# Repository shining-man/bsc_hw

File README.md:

# Battery safety controller (BSC)
This is the PCB for the Battery safety controller.<br>
More information in the wiki and in the discussions of the bsc_fw project.<br>
[BSC Project](https://github.com/shining-man/bsc_fw)<br>
[Wiki (German)](https://github.com/shining-man/bsc_fw/wiki)<br>
[Discussions](https://github.com/shining-man/bsc_fw/discussions)<br>
<br>

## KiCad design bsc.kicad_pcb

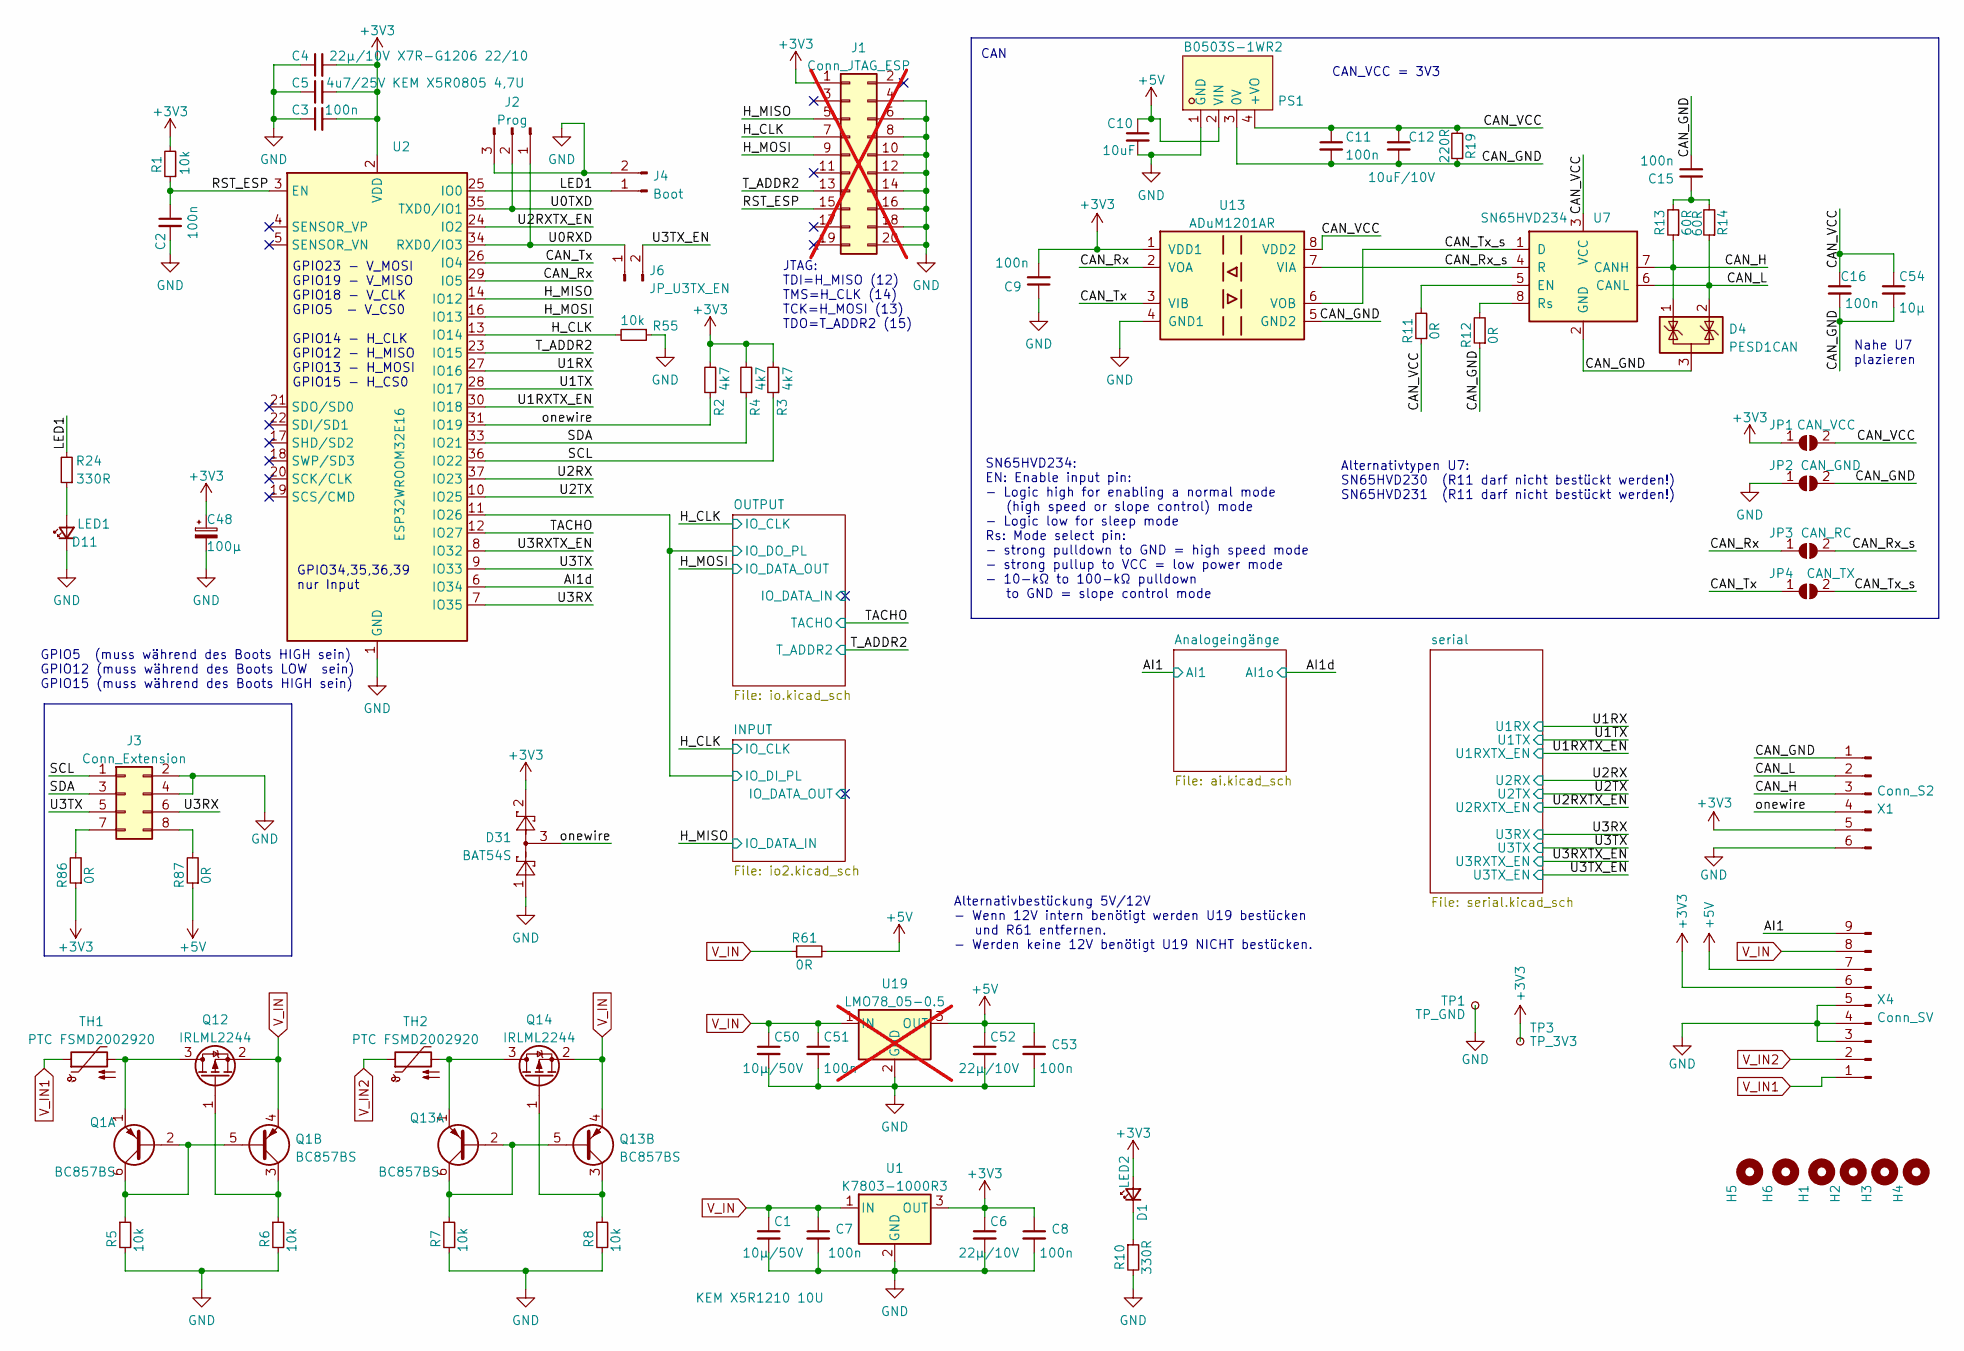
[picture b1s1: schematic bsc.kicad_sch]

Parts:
C1, C50: 10µ/50V; C_1206_3216Metric
C2, C3, C7, C8, C9, C11, C15, C16, C51, C53: 100n; C_0603_1608Metric
C4, C6, C52: 22µ/10V; C_1206_3216Metric
C5: 4u7/25V; C_0805_2012Metric
C10: 10uF; C_0603_1608Metric
C12: 10uF/10V; C_1206_3216Metric
C48: 100µ; CP_Elec_6.3x5.9
C54: 10µ; C_0805_2012Metric
D1: LED2; LED_0603_1608Metric
D4: PESD1CAN; SOT-23
D11: LED1; LED_0603_1608Metric
D31: BAT54S; SOT-23
H1, H2, H3, H4, H5, H6: MountingHole; MountingHole_3.2mm_M3
J1: Conn_JTAG_ESP; PinHeader_2x10_P1.27mm_Vertical_SMD; not fitted
J2: Prog; PinHeader_1x03_P2.54mm_Vertical_jlc
J3: Conn_Extension; PinHeader_2x04_P2.54mm_Vertical_jlc
J4: Boot; PinHeader_1x02_P2.54mm_Vertical_jlc
J6: JP_U3TX_EN; PinHeader_1x02_P2.54mm_Vertical_jlc
JP1: CAN_VCC; SolderJumper-2_P1.3mm_Open_RoundedPad1.0x1.5mm
JP2: CAN_GND; SolderJumper-2_P1.3mm_Open_RoundedPad1.0x1.5mm
JP3: CAN_RC; SolderJumper-2_P1.3mm_Open_RoundedPad1.0x1.5mm
JP4: CAN_TX; SolderJumper-2_P1.3mm_Open_RoundedPad1.0x1.5mm
PS1: B0503S-1WR2; PWRM-TH_DEXU_BXXXXS-1WR2; LCSC Part C5127059
Q1, Q13: BC857BS; SOT-363_SC-70-6
Q12, Q14: IRLML2244; SOT-23
R1, R5, R6, R7, R8, R55: 10k; R_0603_1608Metric
R2, R3, R4: 4k7; R_0603_1608Metric
R10, R24: 330R; R_0603_1608Metric
R11, R12, R61, R86, R87: 0R; R_0603_1608Metric
R13, R14: 60R; R_0603_1608Metric
R19: 220R; R_0805_2012Metric
TH1, TH2: PTC FSMD2002920; Fuse_2920_7451Metric
TP1: TP_GND; TestPoint_Pad_1.0x1.0mm
TP3: TP_3V3; TestPoint_Pad_1.0x1.0mm
U1: K7803-1000R3; Converter_DCDC_RECOM_R-78E-1.0; LCSC Part C111278
U2: ESP32WROOM32E16; ESP32-WROOM-32
U7: SN65HVD234; SOIC-8_3.9x4.9mm_P1.27mm
U13: ADuM1201AR; SOIC-8_3.9x4.9mm_P1.27mm
U19: LMO78_05-0.5; Converter_DCDC_RECOM_R-78E-1.0; not fitted
X1: Conn_S2; PhoenixContact_MCV_1,5_6-G-3.81_1x06_P3.81mm_Vertical
X4: Conn_SV; PhoenixContact_MCV_1,5_9-G-3.81_1x09_P3.81mm_Vertical

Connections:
+3V3: C3.2, C4.2, C5.2, C6.1, C8.1, C9.2, C48.1, D1.2 (A), D31.2, J1.1, JP1.1 (A), R1.2, R2.2, R3.2, R4.2, R86.1, TP3.1, U1.3 (OUT), U2.2 (VDD), U13.1 (VDD1), X1.5, X4.6; also elsewhere on the board
+5V: C10.1, C52.1, C53.1, PS1.2 (VIN), R61.2, R87.1, U19.3 (OUT), X4.7; also elsewhere on the board
/AI1: X4.9; also elsewhere on the board
/AI1d: U2.6 (IO34); also elsewhere on the board
/CAN_GND: C11.2, C12.2, C15.2, C16.2, C54.2, D4.3 (A), JP2.2 (B), PS1.3 (0V), R12.1, R19.1, U7.2 (GND), U13.5 (GND2), X1.1
/CAN_H: D4.1 (K), R13.1, U7.7 (CANH), X1.3
/CAN_L: D4.2 (K), R14.1, U7.6 (CANL), X1.2
/CAN_Rx: JP3.1 (A), U2.29 (IO5), U13.2 (VOA)
/CAN_Rx_s: JP3.2 (B), U7.4 (R), U13.7 (VIA)
/CAN_Tx: JP4.1 (A), U2.26 (IO4), U13.3 (VIB)
/CAN_Tx_s: JP4.2 (B), U7.1 (D), U13.6 (VOB)
/CAN_VCC: C11.1, C12.1, C16.1, C54.1, JP1.2 (B), PS1.4 (+VO), R11.1, R19.2, U7.3 (VCC), U13.8 (VDD2)
/H_CLK: J1.7, R55.2, U2.13 (IO14); also elsewhere on the board
/H_MISO: J1.5, U2.14 (IO12); also elsewhere on the board
/H_MOSI: J1.9, U2.16 (IO13); also elsewhere on the board
/INPUT/IO_DI_PL: U2.11 (IO26); also elsewhere on the board
/LED1: J4.1, R24.2, U2.25 (IO0)
/SCL: J3.1, R3.1, U2.36 (IO22)
/SDA: J3.3, R4.1, U2.33 (IO21)
/TACHO: U2.12 (IO27); also elsewhere on the board
/T_ADDR2: J1.13, U2.23 (IO15); also elsewhere on the board
/U0RXD: J2.1, J6.1, U2.34 (RXD0/IO3)
/U0TXD: J2.2, U2.35 (TXD0/IO1)
/U1RX: U2.27 (IO16); also elsewhere on the board
/U1RXTX_EN: U2.30 (IO18); also elsewhere on the board
/U1TX: U2.28 (IO17); also elsewhere on the board
/U2RX: U2.37 (IO23); also elsewhere on the board
/U2RXTX_EN: U2.24 (IO2); also elsewhere on the board
/U2TX: U2.10 (IO25); also elsewhere on the board
/U3RX: J3.6, U2.7 (IO35); also elsewhere on the board
/U3RXTX_EN: U2.8 (IO32); also elsewhere on the board
/U3TX: J3.5, U2.9 (IO33); also elsewhere on the board
/U3TX_EN: J6.2; also elsewhere on the board
/onewire: D31.3, R2.1, U2.31 (IO19), X1.4
GND: C1.2, C2.2, C3.1, C4.1, C5.1, C6.2, C7.2, C8.2, C9.1, C10.2, C48.2, C50.2, C51.2, C52.2, C53.2, D11.1 (K), D31.1, J1.4, J1.6, J1.8, J1.10, J1.12, J1.14, J1.16, J1.18, J1.20, J2.3, J3.2, J3.4, J4.2, JP2.1 (A), PS1.1 (GND), R5.2, R6.2, R7.2, R8.2, R10.2, R55.1, TP1.1, U1.2 (GND), U2.1 (GND), U2.15 (GND), U2.38 (GND), U2.39 (GND), U13.4 (GND1), U19.2 (GND), X1.6, X4.3, X4.4, X4.5; also elsewhere on the board
unnamed: C15.1, R13.2, R14.2
unnamed: D1.1 (K), R10.1
unnamed: D11.2 (A), R24.1
unnamed: J3.7, R86.2
unnamed: J3.8, R87.2
unnamed: Q1.2 (B1), Q1.5 (B2), Q1.6 (C1), R5.1
unnamed: Q1.1 (E1), Q12.3 (D), TH1.2
unnamed: Q1.3 (C2), Q12.1 (G), R6.1
unnamed: Q13.2 (B1), Q13.5 (B2), Q13.6 (C1), R7.1
unnamed: Q13.1 (E1), Q14.3 (D), TH2.2
unnamed: Q13.3 (C2), Q14.1 (G), R8.1
unnamed: R11.2, U7.5 (EN)
unnamed: R12.2, U7.8 (Rs)
V_IN: C1.1, C7.1, C50.1, C51.1, Q1.4 (E2), Q12.2 (S), Q13.4 (E2), Q14.2 (S), R61.1, U1.1 (IN), U19.1 (IN), X4.8; also elsewhere on the board
V_IN1: TH1.1, X4.1
V_IN2: TH2.1, X4.2

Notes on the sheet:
SN65HVD234: EN: Enable input pin: - Logic high for enabling a normal mode (high speed or slope control) mode - Logic low for sleep mode Rs: Mode select pin: - strong pulldown to GND = high speed mode - strong pullup to VCC = low power mode - 10-kΩ to 100-kΩ pulldown to GND = slope control mode
GPIO23 - V_MOSI GPIO19 - V_MISO GPIO18 - V_CLK GPIO5 - V_CS0 GPIO14 - H_CLK GPIO12 - H_MISO GPIO13 - H_MOSI GPIO15 - H_CS0
JTAG: TDI=H_MISO (12) TMS=H_CLK (14) TCK=H_MOSI (13) TDO=T_ADDR2 (15)
CAN
CAN_VCC = 3V3
Alternativtypen U7: SN65HVD230 (R11 darf nicht bestückt werden!) SN65HVD231 (R11 darf nicht bestückt werden!)
Nahe U7 plazieren
GPIO5 (muss während des Boots HIGH sein) GPIO12 (muss während des Boots LOW sein) GPIO15 (muss während des Boots HIGH sein)
Alternativbestückung 5V/12V - Wenn 12V intern benötigt werden U19 bestücken und R61 entfernen. - Werden keine 12V benötigt U19 NICHT bestücken.
GPIO34,35,36,39 nur Input

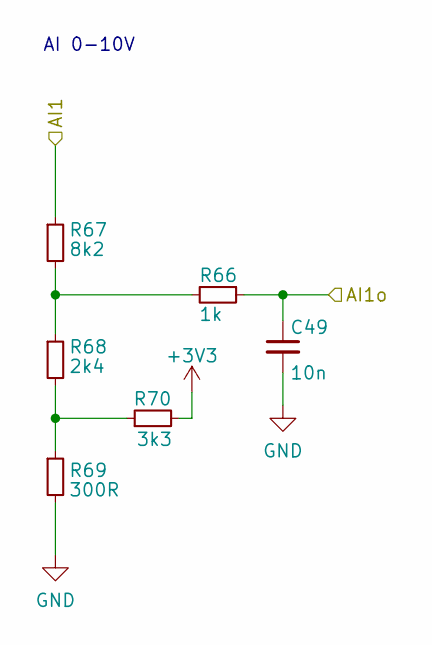
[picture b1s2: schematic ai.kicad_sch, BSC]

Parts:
C49: 10n; C_0603_1608Metric
R66: 1k; R_0603_1608Metric
R67: 8k2; R_0603_1608Metric
R68: 2k4; R_0603_1608Metric
R69: 300R; R_0603_1608Metric
R70: 3k3; R_0603_1608Metric

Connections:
+3V3: R70.2; also elsewhere on the board
/AI1: R67.1; also elsewhere on the board
/AI1d: C49.1, R66.1; also elsewhere on the board
GND: C49.2, R69.2; also elsewhere on the board
unnamed: R66.2, R67.2, R68.1
unnamed: R68.2, R69.1, R70.1

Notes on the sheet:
AI 0-10V

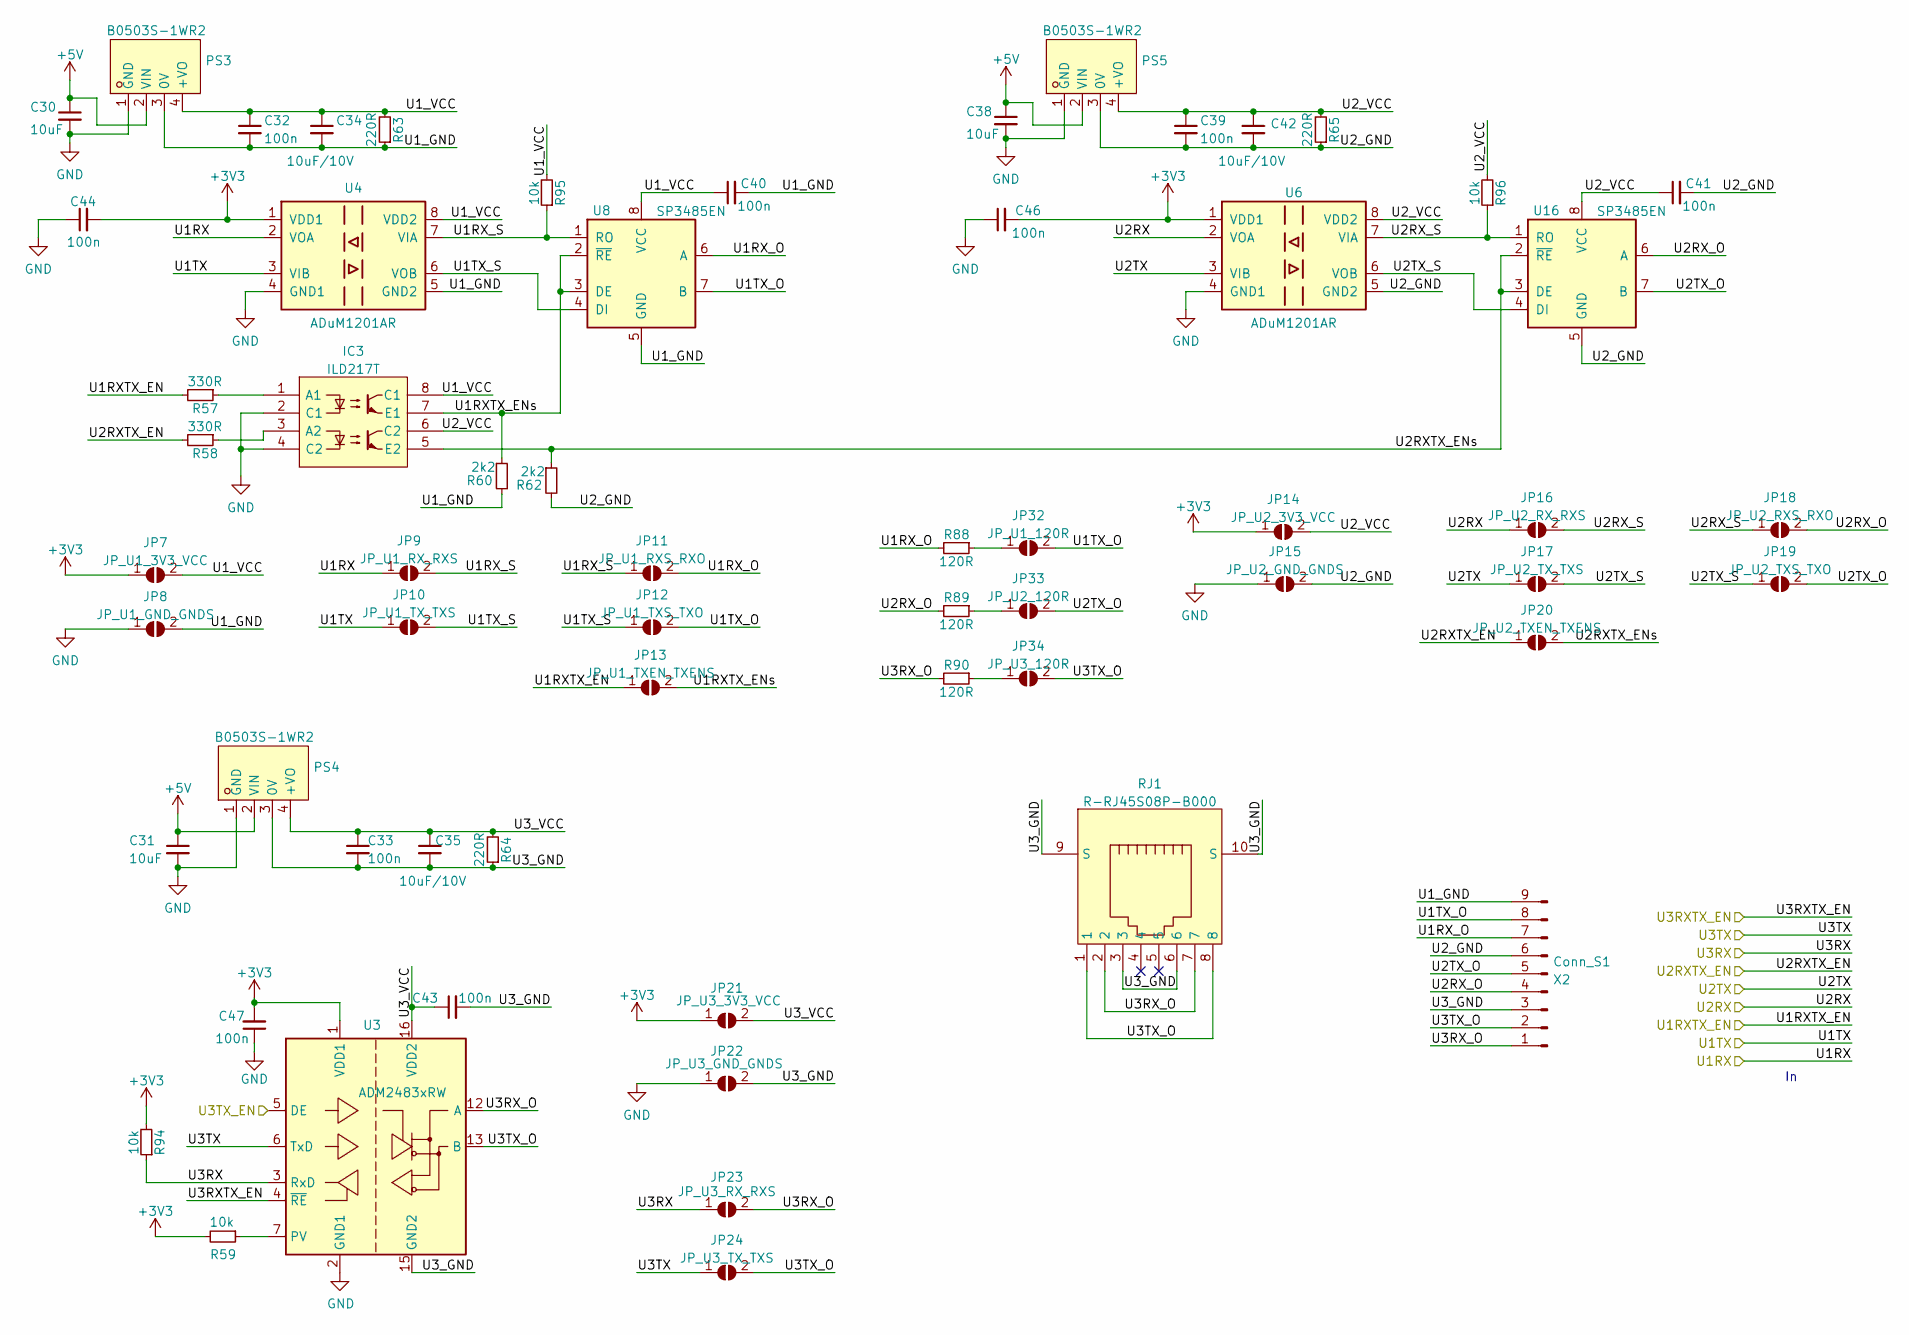
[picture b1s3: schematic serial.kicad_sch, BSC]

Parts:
C30, C31, C38: 10uF; C_0603_1608Metric
C32, C33, C39, C40, C41, C43, C44, C46, C47: 100n; C_0603_1608Metric
C34, C35, C42: 10uF/10V; C_1206_3216Metric
IC3: ILD217T; SOIC-8_3.9x4.9mm_P1.27mm; Mouser Part Number 782-ILD217T
JP7: JP_U1_3V3_VCC; SolderJumper-2_P1.3mm_Open_RoundedPad1.0x1.5mm
JP8: JP_U1_GND_GNDS; SolderJumper-2_P1.3mm_Open_RoundedPad1.0x1.5mm
JP9: JP_U1_RX_RXS; SolderJumper-2_P1.3mm_Open_RoundedPad1.0x1.5mm
JP10: JP_U1_TX_TXS; SolderJumper-2_P1.3mm_Open_RoundedPad1.0x1.5mm
JP11: JP_U1_RXS_RXO; SolderJumper-2_P1.3mm_Open_RoundedPad1.0x1.5mm
JP12: JP_U1_TXS_TXO; SolderJumper-2_P1.3mm_Open_RoundedPad1.0x1.5mm
JP13: JP_U1_TXEN_TXENS; SolderJumper-2_P1.3mm_Open_RoundedPad1.0x1.5mm
JP14: JP_U2_3V3_VCC; SolderJumper-2_P1.3mm_Open_RoundedPad1.0x1.5mm
JP15: JP_U2_GND_GNDS; SolderJumper-2_P1.3mm_Open_RoundedPad1.0x1.5mm
JP16: JP_U2_RX_RXS; SolderJumper-2_P1.3mm_Open_RoundedPad1.0x1.5mm
JP17: JP_U2_TX_TXS; SolderJumper-2_P1.3mm_Open_RoundedPad1.0x1.5mm
JP18: JP_U2_RXS_RXO; SolderJumper-2_P1.3mm_Open_RoundedPad1.0x1.5mm
JP19: JP_U2_TXS_TXO; SolderJumper-2_P1.3mm_Open_RoundedPad1.0x1.5mm
JP20: JP_U2_TXEN_TXENS; SolderJumper-2_P1.3mm_Open_RoundedPad1.0x1.5mm
JP21: JP_U3_3V3_VCC; SolderJumper-2_P1.3mm_Open_RoundedPad1.0x1.5mm
JP22: JP_U3_GND_GNDS; SolderJumper-2_P1.3mm_Open_RoundedPad1.0x1.5mm
JP23: JP_U3_RX_RXS; SolderJumper-2_P1.3mm_Open_RoundedPad1.0x1.5mm
JP24: JP_U3_TX_TXS; SolderJumper-2_P1.3mm_Open_RoundedPad1.0x1.5mm
JP32: JP_U1_120R; SolderJumper-2_P1.3mm_Open_RoundedPad1.0x1.5mm
JP33: JP_U2_120R; SolderJumper-2_P1.3mm_Open_RoundedPad1.0x1.5mm
JP34: JP_U3_120R; SolderJumper-2_P1.3mm_Open_RoundedPad1.0x1.5mm
PS3, PS4, PS5: B0503S-1WR2; PWRM-TH_DEXU_BXXXXS-1WR2; LCSC Part C5127059
R57, R58: 330R; R_0603_1608Metric
R59, R94, R95, R96: 10k; R_0603_1608Metric
R60, R62: 2k2; R_0603_1608Metric
R63, R64, R65: 220R; R_0805_2012Metric
R88, R89, R90: 120R; R_0603_1608Metric
RJ1: R-RJ45S08P-B000; RJ45-TH_R-RJ45S08P-B000; LCSC Part C386763
U3: ADM2483xRW; SOIC-16W_7.5x10.3mm_P1.27mm; PartNumber ADM2483BRWZ-REEL; LCSCStockCode C9637
U4, U6: ADuM1201AR; SOIC-8_3.9x4.9mm_P1.27mm
U8, U16: SP3485EN; SOIC-8_3.9x4.9mm_P1.27mm
X2: Conn_S1; PhoenixContact_MCV_1,5_9-G-3.81_1x09_P3.81mm_Vertical

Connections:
+3V3: C44.2, C46.2, C47.2, JP7.1 (A), JP14.1 (A), JP21.1 (A), R59.2, R94.2, U3.1 (VDD1), U4.1 (VDD1), U6.1 (VDD1); also elsewhere on the board
+5V: C30.1, C31.1, C38.1, PS3.2 (VIN), PS4.2 (VIN), PS5.2 (VIN); also elsewhere on the board
/U1RX: JP9.1 (A), U4.2 (VOA); also elsewhere on the board
/U1RXTX_EN: JP13.1 (A), R57.2; also elsewhere on the board
/U1TX: JP10.1 (A), U4.3 (VIB); also elsewhere on the board
/U2RX: JP16.1 (A), U6.2 (VOA); also elsewhere on the board
/U2RXTX_EN: JP20.1 (A), R58.2; also elsewhere on the board
/U2TX: JP17.1 (A), U6.3 (VIB); also elsewhere on the board
/U3RX: JP23.1 (A), R94.1, U3.3 (RxD); also elsewhere on the board
/U3RXTX_EN: U3.4 (~RE); also elsewhere on the board
/U3TX: JP24.1 (A), U3.6 (TxD); also elsewhere on the board
/U3TX_EN: U3.5 (DE); also elsewhere on the board
/serial/U1RXTX_ENs: IC3.7 (E1), JP13.2 (B), R60.1, U8.2 (~RE), U8.3 (DE)
/serial/U1RX_O: JP11.2 (B), R88.2, U8.6 (A), X2.7
/serial/U1RX_S: JP9.2 (B), JP11.1 (A), R95.1, U4.7 (VIA), U8.1 (RO)
/serial/U1TX_O: JP12.2 (B), JP32.2 (B), U8.7 (B), X2.8
/serial/U1TX_S: JP10.2 (B), JP12.1 (A), U4.6 (VOB), U8.4 (DI)
/serial/U1_GND: C32.2, C34.2, C40.2, JP8.2 (B), PS3.3 (0V), R60.2, R63.1, U4.5 (GND2), U8.5 (GND), X2.9
/serial/U1_VCC: C32.1, C34.1, C40.1, IC3.8 (C1), JP7.2 (B), PS3.4 (+VO), R63.2, R95.2, U4.8 (VDD2), U8.8 (VCC)
/serial/U2RXTX_ENs: IC3.5 (E2), JP20.2 (B), R62.1, U16.2 (~RE), U16.3 (DE)
/serial/U2RX_O: JP18.2 (B), R89.2, U16.6 (A), X2.4
/serial/U2RX_S: JP16.2 (B), JP18.1 (A), R96.1, U6.7 (VIA), U16.1 (RO)
/serial/U2TX_O: JP19.2 (B), JP33.2 (B), U16.7 (B), X2.5
/serial/U2TX_S: JP17.2 (B), JP19.1 (A), U6.6 (VOB), U16.4 (DI)
/serial/U2_GND: C39.2, C41.2, C42.2, JP15.2 (B), PS5.3 (0V), R62.2, R65.1, U6.5 (GND2), U16.5 (GND), X2.6
/serial/U2_VCC: C39.1, C41.1, C42.1, IC3.6 (C2), JP14.2 (B), PS5.4 (+VO), R65.2, R96.2, U6.8 (VDD2), U16.8 (VCC)
/serial/U3RX_O: JP23.2 (B), R90.2, RJ1.2, RJ1.7, U3.12 (A), X2.1
/serial/U3TX_O: JP24.2 (B), JP34.2 (B), RJ1.1, RJ1.8, U3.13 (B), X2.2
/serial/U3_GND: C33.2, C35.2, C43.2, JP22.2 (B), PS4.3 (0V), R64.1, RJ1.3, RJ1.6, RJ1.9 (S), RJ1.10 (S), U3.9 (GND2), U3.15 (GND2), X2.3
/serial/U3_VCC: C33.1, C35.1, C43.1, JP21.2 (B), PS4.4 (+VO), R64.2, U3.16 (VDD2)
GND: C30.2, C31.2, C38.2, C44.1, C46.1, C47.1, IC3.2 (C1), IC3.4 (C2), JP8.1 (A), JP15.1 (A), JP22.1 (A), PS3.1 (GND), PS4.1 (GND), PS5.1 (GND), U3.2 (GND1), U3.8 (GND1), U4.4 (GND1), U6.4 (GND1); also elsewhere on the board
unnamed: IC3.1 (A1), R57.1
unnamed: IC3.3 (A2), R58.1
unnamed: JP32.1 (A), R88.1
unnamed: JP33.1 (A), R89.1
unnamed: JP34.1 (A), R90.1
unnamed: R59.1, U3.7 (PV)

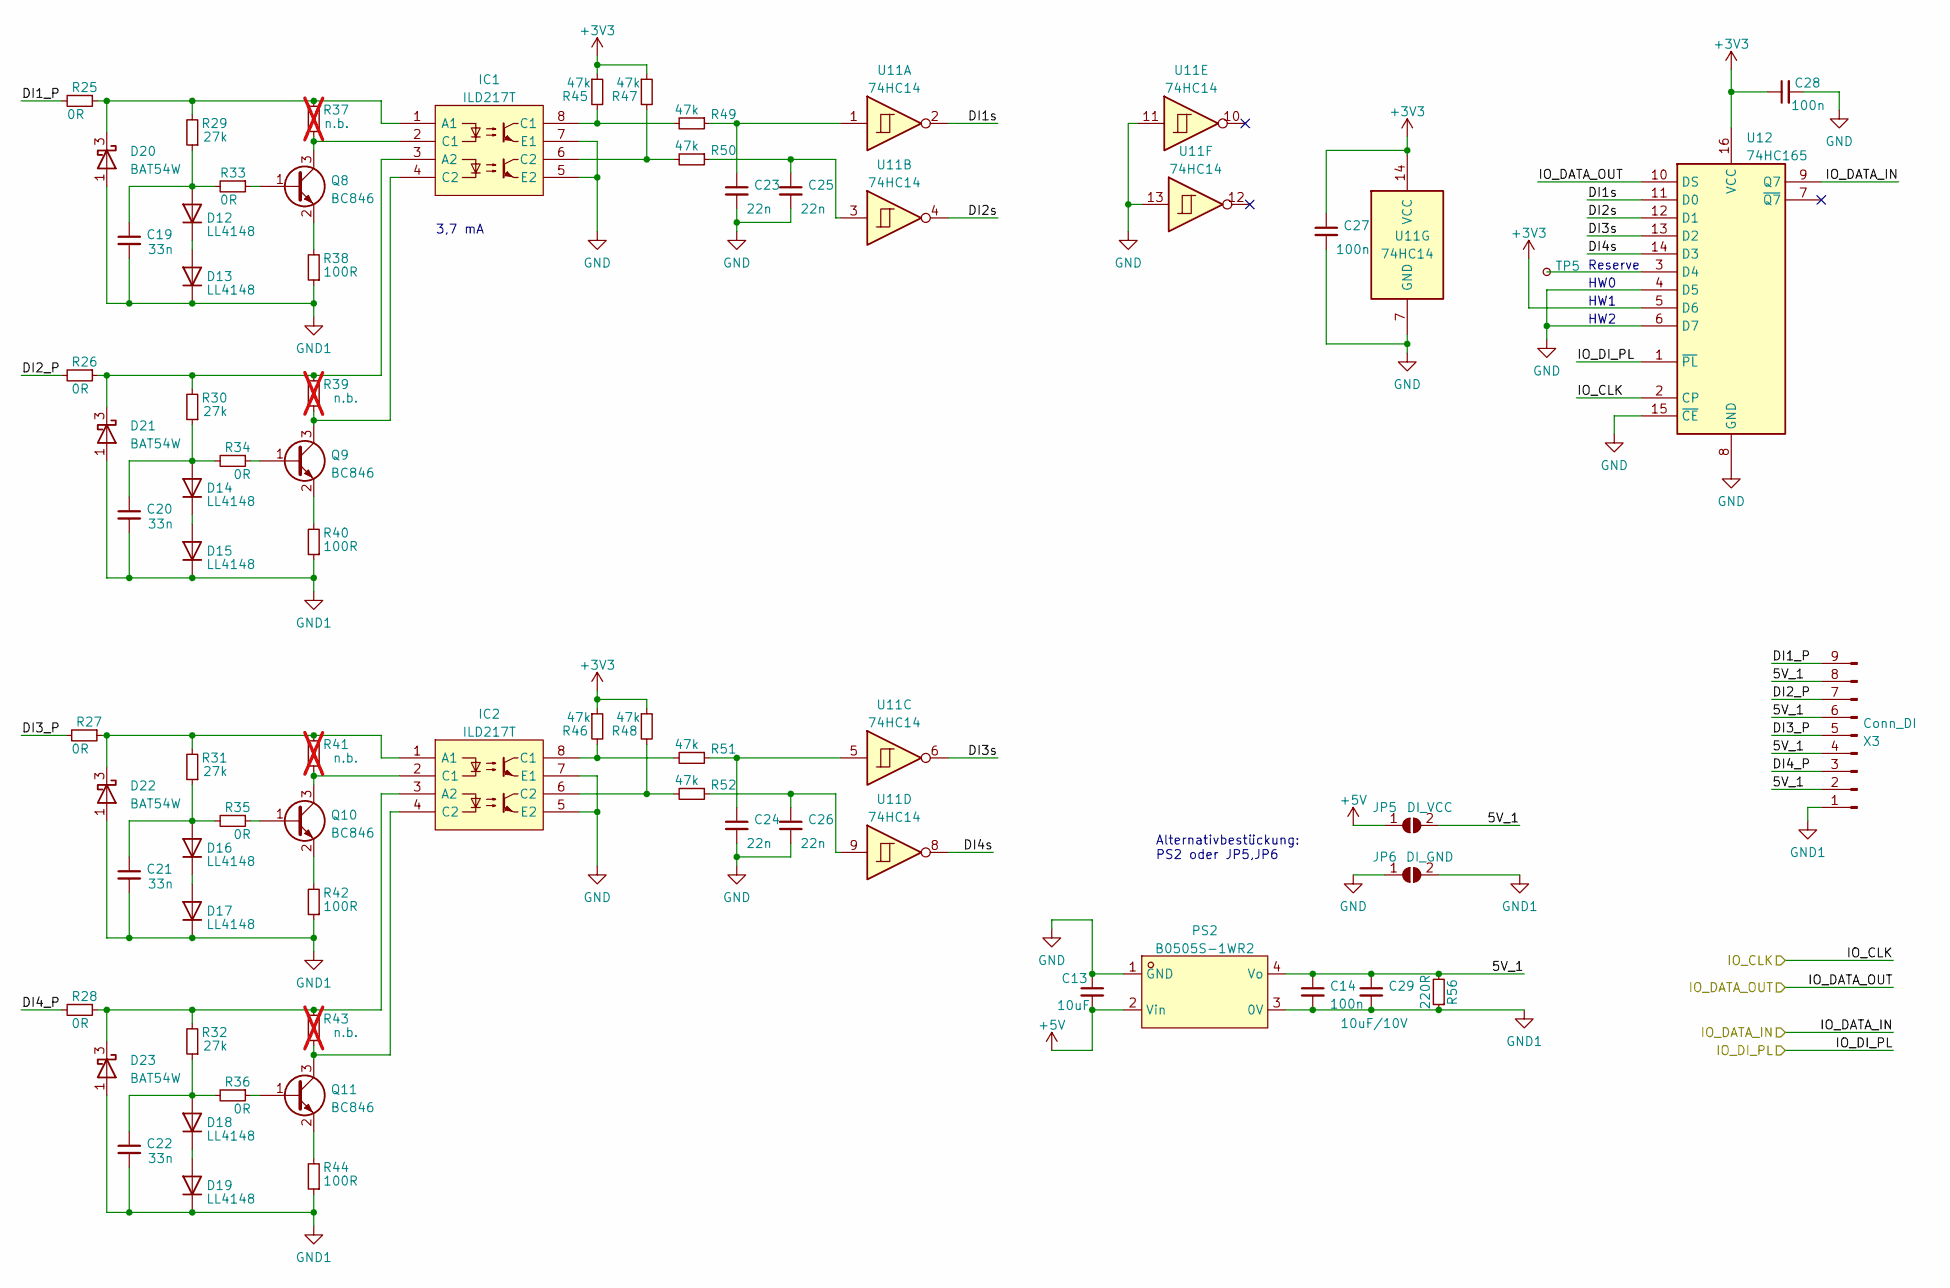
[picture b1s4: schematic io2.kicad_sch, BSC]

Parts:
C13: 10uF; C_0603_1608Metric
C14, C27, C28: 100n; C_0603_1608Metric
C19, C20, C21, C22: 33n; C_0603_1608Metric
C23, C24, C25, C26: 22n; C_0603_1608Metric
C29: 10uF/10V; C_1206_3216Metric
D12, D13, D14, D15, D16, D17, D18, D19: LL4148; D_MiniMELF
D20, D21, D22, D23: BAT54W; SOT-323_SC-70
IC1, IC2: ILD217T; SOIC-8_3.9x4.9mm_P1.27mm; Mouser Part Number 782-ILD217T
JP5: DI_VCC; SolderJumper-2_P1.3mm_Open_RoundedPad1.0x1.5mm
JP6: DI_GND; SolderJumper-2_P1.3mm_Open_RoundedPad1.0x1.5mm
PS2: B0505S-1WR2; PWRM-TH_BXXXXS-1WR3; LCSC Part C909796
Q8, Q9, Q10, Q11: BC846; SOT-23
R25, R26, R27, R28, R33, R34, R35, R36: 0R; R_0603_1608Metric
R29, R30, R31, R32: 27k; R_0603_1608Metric
R37, R39, R41, R43: n.b.; R_0603_1608Metric; not fitted
R38, R40, R42, R44: 100R; R_0603_1608Metric
R45, R46, R47, R48, R49, R50, R51, R52: 47k; R_0603_1608Metric
R56: 220R; R_0805_2012Metric
TP5: TP; TestPoint_Pad_1.0x1.0mm
U11: 74HC14; SO-14_3.9x8.65mm_P1.27mm
U12: 74HC165; SOIC-16_3.9x9.9mm_P1.27mm
X3: Conn_DI; PhoenixContact_MCV_1,5_9-G-3.81_1x09_P3.81mm_Vertical

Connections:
+3V3: C27.1, C28.1, R45.1, R46.1, R47.1, R48.1, U11.14 (VCC), U12.5 (D6), U12.16 (VCC); also elsewhere on the board
+5V: C13.2, JP5.1 (A), PS2.2 (Vin); also elsewhere on the board
/H_CLK: U12.2 (CP); also elsewhere on the board
/H_MISO: U12.9 (Q7); also elsewhere on the board
/INPUT/5V_1: C14.1, C29.1, JP5.2 (B), PS2.4 (Vo), R56.2, X3.2, X3.4, X3.6, X3.8
/INPUT/DI1_P: R25.2, X3.9
/INPUT/DI1s: U11.2, U12.11 (D0)
/INPUT/DI2_P: R26.2, X3.7
/INPUT/DI2s: U11.4, U12.12 (D1)
/INPUT/DI3_P: R27.2, X3.5
/INPUT/DI3s: U11.6, U12.13 (D2)
/INPUT/DI4_P: R28.2, X3.3
/INPUT/DI4s: U11.8, U12.14 (D3)
/INPUT/IO_DATA_OUT: U12.10 (DS)
/INPUT/IO_DI_PL: U12.1 (~PL); also elsewhere on the board
GND: C13.1, C23.2, C24.2, C25.2, C26.2, C27.2, C28.2, IC1.5 (E2), IC1.7 (E1), IC2.5 (E2), IC2.7 (E1), JP6.1 (A), PS2.1 (GND), U11.7 (GND), U11.11, U11.13, U12.4 (D5), U12.6 (D7), U12.8 (GND), U12.15 (~CE); also elsewhere on the board
GND1: C14.2, C19.2, C20.2, C21.2, C22.2, C29.2, D13.1 (K), D15.1 (K), D17.1 (K), D19.1 (K), D20.1 (A), D21.1 (A), D22.1 (A), D23.1 (A), JP6.2 (B), PS2.3 (0V), R38.1, R40.1, R42.1, R44.1, R56.1, X3.1
unnamed: C23.1, R49.1, U11.1
unnamed: C24.1, R51.1, U11.5
unnamed: C25.1, R50.1, U11.3
unnamed: C26.1, R52.1, U11.9
unnamed: C19.1, D12.2 (A), R29.1, R33.2
unnamed: D12.1 (K), D13.2 (A)
unnamed: C20.1, D14.2 (A), R30.1, R34.2
unnamed: D14.1 (K), D15.2 (A)
unnamed: C21.1, D16.2 (A), R31.1, R35.2
unnamed: D16.1 (K), D17.2 (A)
unnamed: C22.1, D18.2 (A), R32.1, R36.2
unnamed: D18.1 (K), D19.2 (A)
unnamed: D20.3 (K), IC1.1 (A1), R25.1, R29.2, R37.2
unnamed: D21.3 (K), IC1.3 (A2), R26.1, R30.2, R39.2
unnamed: D22.3 (K), IC2.1 (A1), R27.1, R31.2, R41.2
unnamed: D23.3 (K), IC2.3 (A2), R28.1, R32.2, R43.2
unnamed: IC1.8 (C1), R45.2, R49.2
unnamed: IC1.6 (C2), R47.2, R50.2
unnamed: IC2.8 (C1), R46.2, R51.2
unnamed: IC2.6 (C2), R48.2, R52.2
unnamed: Q8.1 (B), R33.1
unnamed: IC1.2 (C1), Q8.3 (C), R37.1
unnamed: Q8.2 (E), R38.2
unnamed: Q9.1 (B), R34.1
unnamed: IC1.4 (C2), Q9.3 (C), R39.1
unnamed: Q9.2 (E), R40.2
unnamed: Q10.1 (B), R35.1
unnamed: IC2.2 (C1), Q10.3 (C), R41.1
unnamed: Q10.2 (E), R42.2
unnamed: Q11.1 (B), R36.1
unnamed: IC2.4 (C2), Q11.3 (C), R43.1
unnamed: Q11.2 (E), R44.2
unnamed: TP5.1, U12.3 (D4)

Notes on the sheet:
Reserve
HW0
HW2
HW1
3,7 mA
Alternativbestückung: PS2 oder JP5,JP6

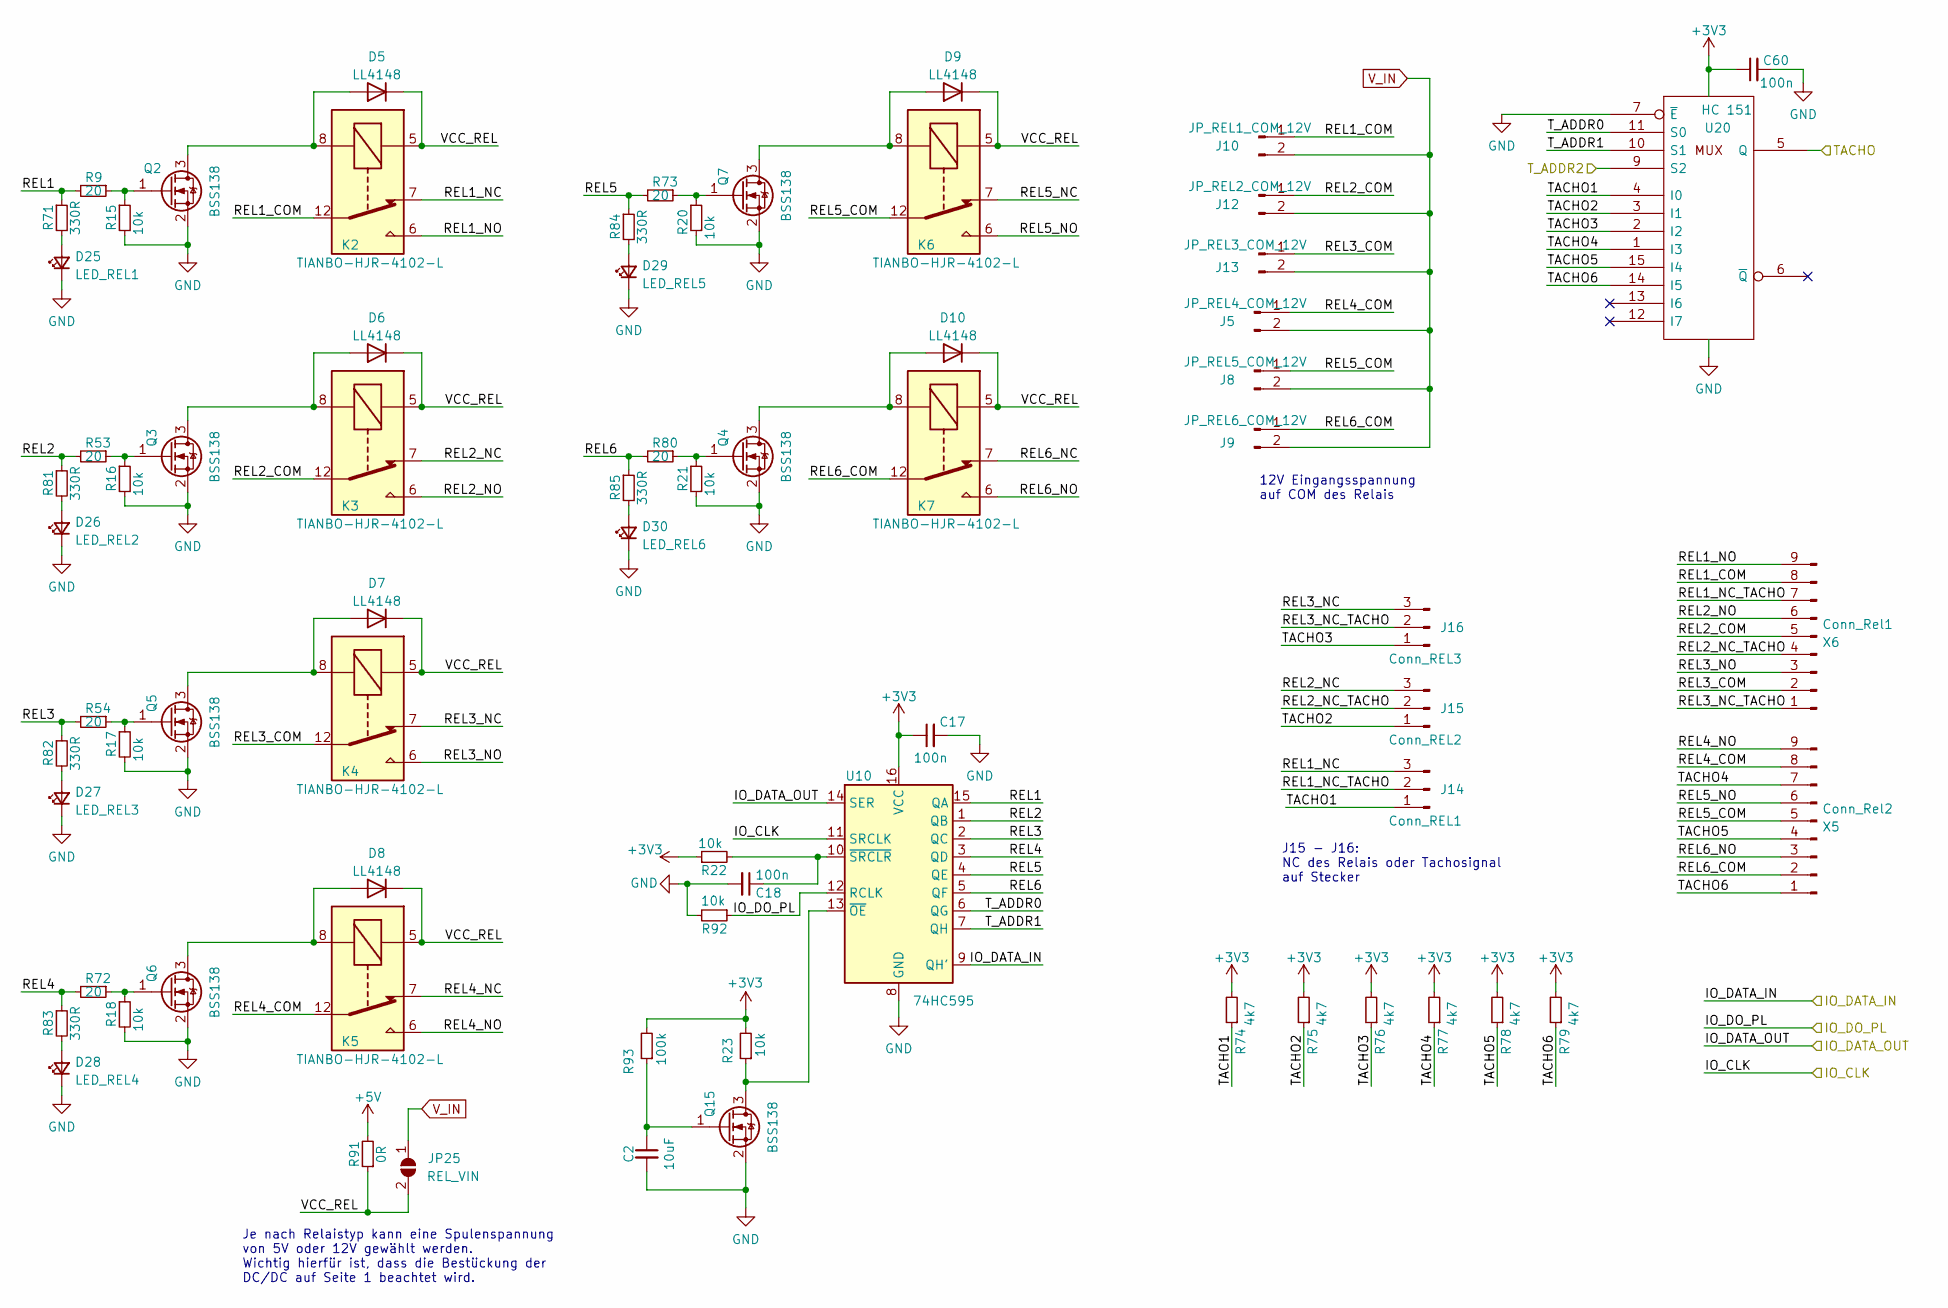
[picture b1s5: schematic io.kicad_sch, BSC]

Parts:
C2: 10uF; C_0603_1608Metric; LCSC Part C96446
C17, C18, C60: 100n; C_0603_1608Metric
D5, D6, D7, D8, D9, D10: LL4148; D_MiniMELF
D25: LED_REL1; LED_0603_1608Metric
D26: LED_REL2; LED_0603_1608Metric
D27: LED_REL3; LED_0603_1608Metric
D28: LED_REL4; LED_0603_1608Metric
D29: LED_REL5; LED_0603_1608Metric
D30: LED_REL6; LED_0603_1608Metric
J5: JP_REL4_COM_12V; PinHeader_1x02_P2.54mm_Vertical_jlc
J8: JP_REL5_COM_12V; PinHeader_1x02_P2.54mm_Vertical_jlc
J9: JP_REL6_COM_12V; PinHeader_1x02_P2.54mm_Vertical_jlc
J10: JP_REL1_COM_12V; PinHeader_1x02_P2.54mm_Vertical_jlc
J12: JP_REL2_COM_12V; PinHeader_1x02_P2.54mm_Vertical_jlc
J13: JP_REL3_COM_12V; PinHeader_1x02_P2.54mm_Vertical_jlc
J14: Conn_REL1; PinHeader_1x03_P2.54mm_Vertical_jlc
J15: Conn_REL2; PinHeader_1x03_P2.54mm_Vertical_jlc
J16: Conn_REL3; PinHeader_1x03_P2.54mm_Vertical_jlc
JP25: REL_VIN; SolderJumper-2_P1.3mm_Open_RoundedPad1.0x1.5mm
K2, K3, K4, K5, K6, K7: TIANBO-HJR-4102-L; Relay_SPDT_HJR-4102
Q2, Q3, Q4, Q5, Q6, Q7, Q15: BSS138; SOT-23
R9, R53, R54, R72, R73, R80: 20; R_0603_1608Metric
R15, R16, R17, R18, R20, R21, R22, R23, R92: 10k; R_0603_1608Metric
R71, R81, R82, R83, R84, R85: 330R; R_0603_1608Metric
R74, R75, R76, R77, R78, R79: 4k7; R_0603_1608Metric
R91: 0R; R_0603_1608Metric
R93: 100k; R_0603_1608Metric
U10: 74HC595; SOIC-16_3.9x9.9mm_P1.27mm
U20: HC 151; SOIC-16_3.9x9.9mm_P1.27mm
X5: Conn_Rel2; PhoenixContact_MCV_1,5_9-G-3.81_1x09_P3.81mm_Vertical
X6: Conn_Rel1; PhoenixContact_MCV_1,5_9-G-3.81_1x09_P3.81mm_Vertical

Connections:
+3V3: C17.1, C60.1, R22.1, R23.2, R74.2, R75.2, R76.2, R77.2, R78.2, R79.2, R93.2, U10.16 (VCC), U20.16 (VCC); also elsewhere on the board
+5V: R91.2; also elsewhere on the board
/H_CLK: U10.11 (SRCLK); also elsewhere on the board
/H_MOSI: U10.14 (SER); also elsewhere on the board
/INPUT/IO_DI_PL: R92.1, U10.12 (RCLK); also elsewhere on the board
/OUTPUT/IO_DATA_IN: U10.9 (QH')
/OUTPUT/REL1: R9.2, R71.1, U10.15 (QA)
/OUTPUT/REL1_COM: J10.1, K2.12, X6.8
/OUTPUT/REL1_NC: J14.3, K2.7
/OUTPUT/REL1_NC_TACHO: J14.2, X6.7
/OUTPUT/REL1_NO: K2.6, X6.9
/OUTPUT/REL2: R53.2, R81.1, U10.1 (QB)
/OUTPUT/REL2_COM: J12.1, K3.12, X6.5
/OUTPUT/REL2_NC: J15.3, K3.7
/OUTPUT/REL2_NC_TACHO: J15.2, X6.4
/OUTPUT/REL2_NO: K3.6, X6.6
/OUTPUT/REL3: R54.2, R82.1, U10.2 (QC)
/OUTPUT/REL3_COM: J13.1, K4.12, X6.2
/OUTPUT/REL3_NC: J16.3, K4.7
/OUTPUT/REL3_NC_TACHO: J16.2, X6.1
/OUTPUT/REL3_NO: K4.6, X6.3
/OUTPUT/REL4: R72.2, R83.1, U10.3 (QD)
/OUTPUT/REL4_COM: J5.1, K5.12, X5.8
/OUTPUT/REL4_NC: K5.7
/OUTPUT/REL4_NO: K5.6, X5.9
/OUTPUT/REL5: R73.2, R84.1, U10.4 (QE)
/OUTPUT/REL5_COM: J8.1, K6.12, X5.5
/OUTPUT/REL5_NC: K6.7
/OUTPUT/REL5_NO: K6.6, X5.6
/OUTPUT/REL6: R80.2, R85.1, U10.5 (QF)
/OUTPUT/REL6_COM: J9.1, K7.12, X5.2
/OUTPUT/REL6_NC: K7.7
/OUTPUT/REL6_NO: K7.6, X5.3
/OUTPUT/TACHO1: J14.1, R74.1, U20.4 (I0)
/OUTPUT/TACHO2: J15.1, R75.1, U20.3 (I1)
/OUTPUT/TACHO3: J16.1, R76.1, U20.2 (I2)
/OUTPUT/TACHO4: R77.1, U20.1 (I3), X5.7
/OUTPUT/TACHO5: R78.1, U20.15 (I4), X5.4
/OUTPUT/TACHO6: R79.1, U20.14 (I5), X5.1
/OUTPUT/T_ADDR0: U10.6 (QG), U20.11 (S0)
/OUTPUT/T_ADDR1: U10.7 (QH), U20.10 (S1)
/OUTPUT/VCC_REL: D5.1 (K), D6.1 (K), D7.1 (K), D8.1 (K), D9.1 (K), D10.1 (K), JP25.2 (B), K2.5, K3.5, K4.5, K5.5, K6.5, K7.5, R91.1
/TACHO: U20.5 (Q); also elsewhere on the board
/T_ADDR2: U20.9 (S2); also elsewhere on the board
GND: C2.2, C17.2, C18.2, C60.2, D25.1 (K), D26.1 (K), D27.1 (K), D28.1 (K), D29.1 (K), D30.1 (K), Q2.2 (S), Q3.2 (S), Q4.2 (S), Q5.2 (S), Q6.2 (S), Q7.2 (S), Q15.2 (S), R15.2, R16.2, R17.2, R18.2, R20.2, R21.2, R92.2, U10.8 (GND), U20.7 (~E), U20.8 (GND); also elsewhere on the board
unnamed: D5.2 (A), K2.8, Q2.3 (D)
unnamed: D6.2 (A), K3.8, Q3.3 (D)
unnamed: D7.2 (A), K4.8, Q5.3 (D)
unnamed: D8.2 (A), K5.8, Q6.3 (D)
unnamed: D9.2 (A), K6.8, Q7.3 (D)
unnamed: D10.2 (A), K7.8, Q4.3 (D)
unnamed: D25.2 (A), R71.2
unnamed: D26.2 (A), R81.2
unnamed: D27.2 (A), R82.2
unnamed: D28.2 (A), R83.2
unnamed: D29.2 (A), R84.2
unnamed: D30.2 (A), R85.2
unnamed: Q2.1 (G), R9.1, R15.1
unnamed: Q3.1 (G), R16.1, R53.1
unnamed: Q4.1 (G), R21.1, R80.1
unnamed: Q5.1 (G), R17.1, R54.1
unnamed: Q6.1 (G), R18.1, R72.1
unnamed: Q7.1 (G), R20.1, R73.1
unnamed: Q15.3 (D), R23.1, U10.13 (~OE)
unnamed: C18.1, R22.2, U10.10 (~SRCLR)
V_IN: J5.2, J8.2, J9.2, J10.2, J12.2, J13.2, JP25.1 (A); also elsewhere on the board

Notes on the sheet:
Je nach Relaistyp kann eine Spulenspannung von 5V oder 12V gewählt werden. Wichtig hierfür ist, dass die Bestückung der DC/DC auf Seite 1 beachtet wird.
12V Eingangsspannung auf COM des Relais
J15 - J16: NC des Relais oder Tachosignal auf Stecker

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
